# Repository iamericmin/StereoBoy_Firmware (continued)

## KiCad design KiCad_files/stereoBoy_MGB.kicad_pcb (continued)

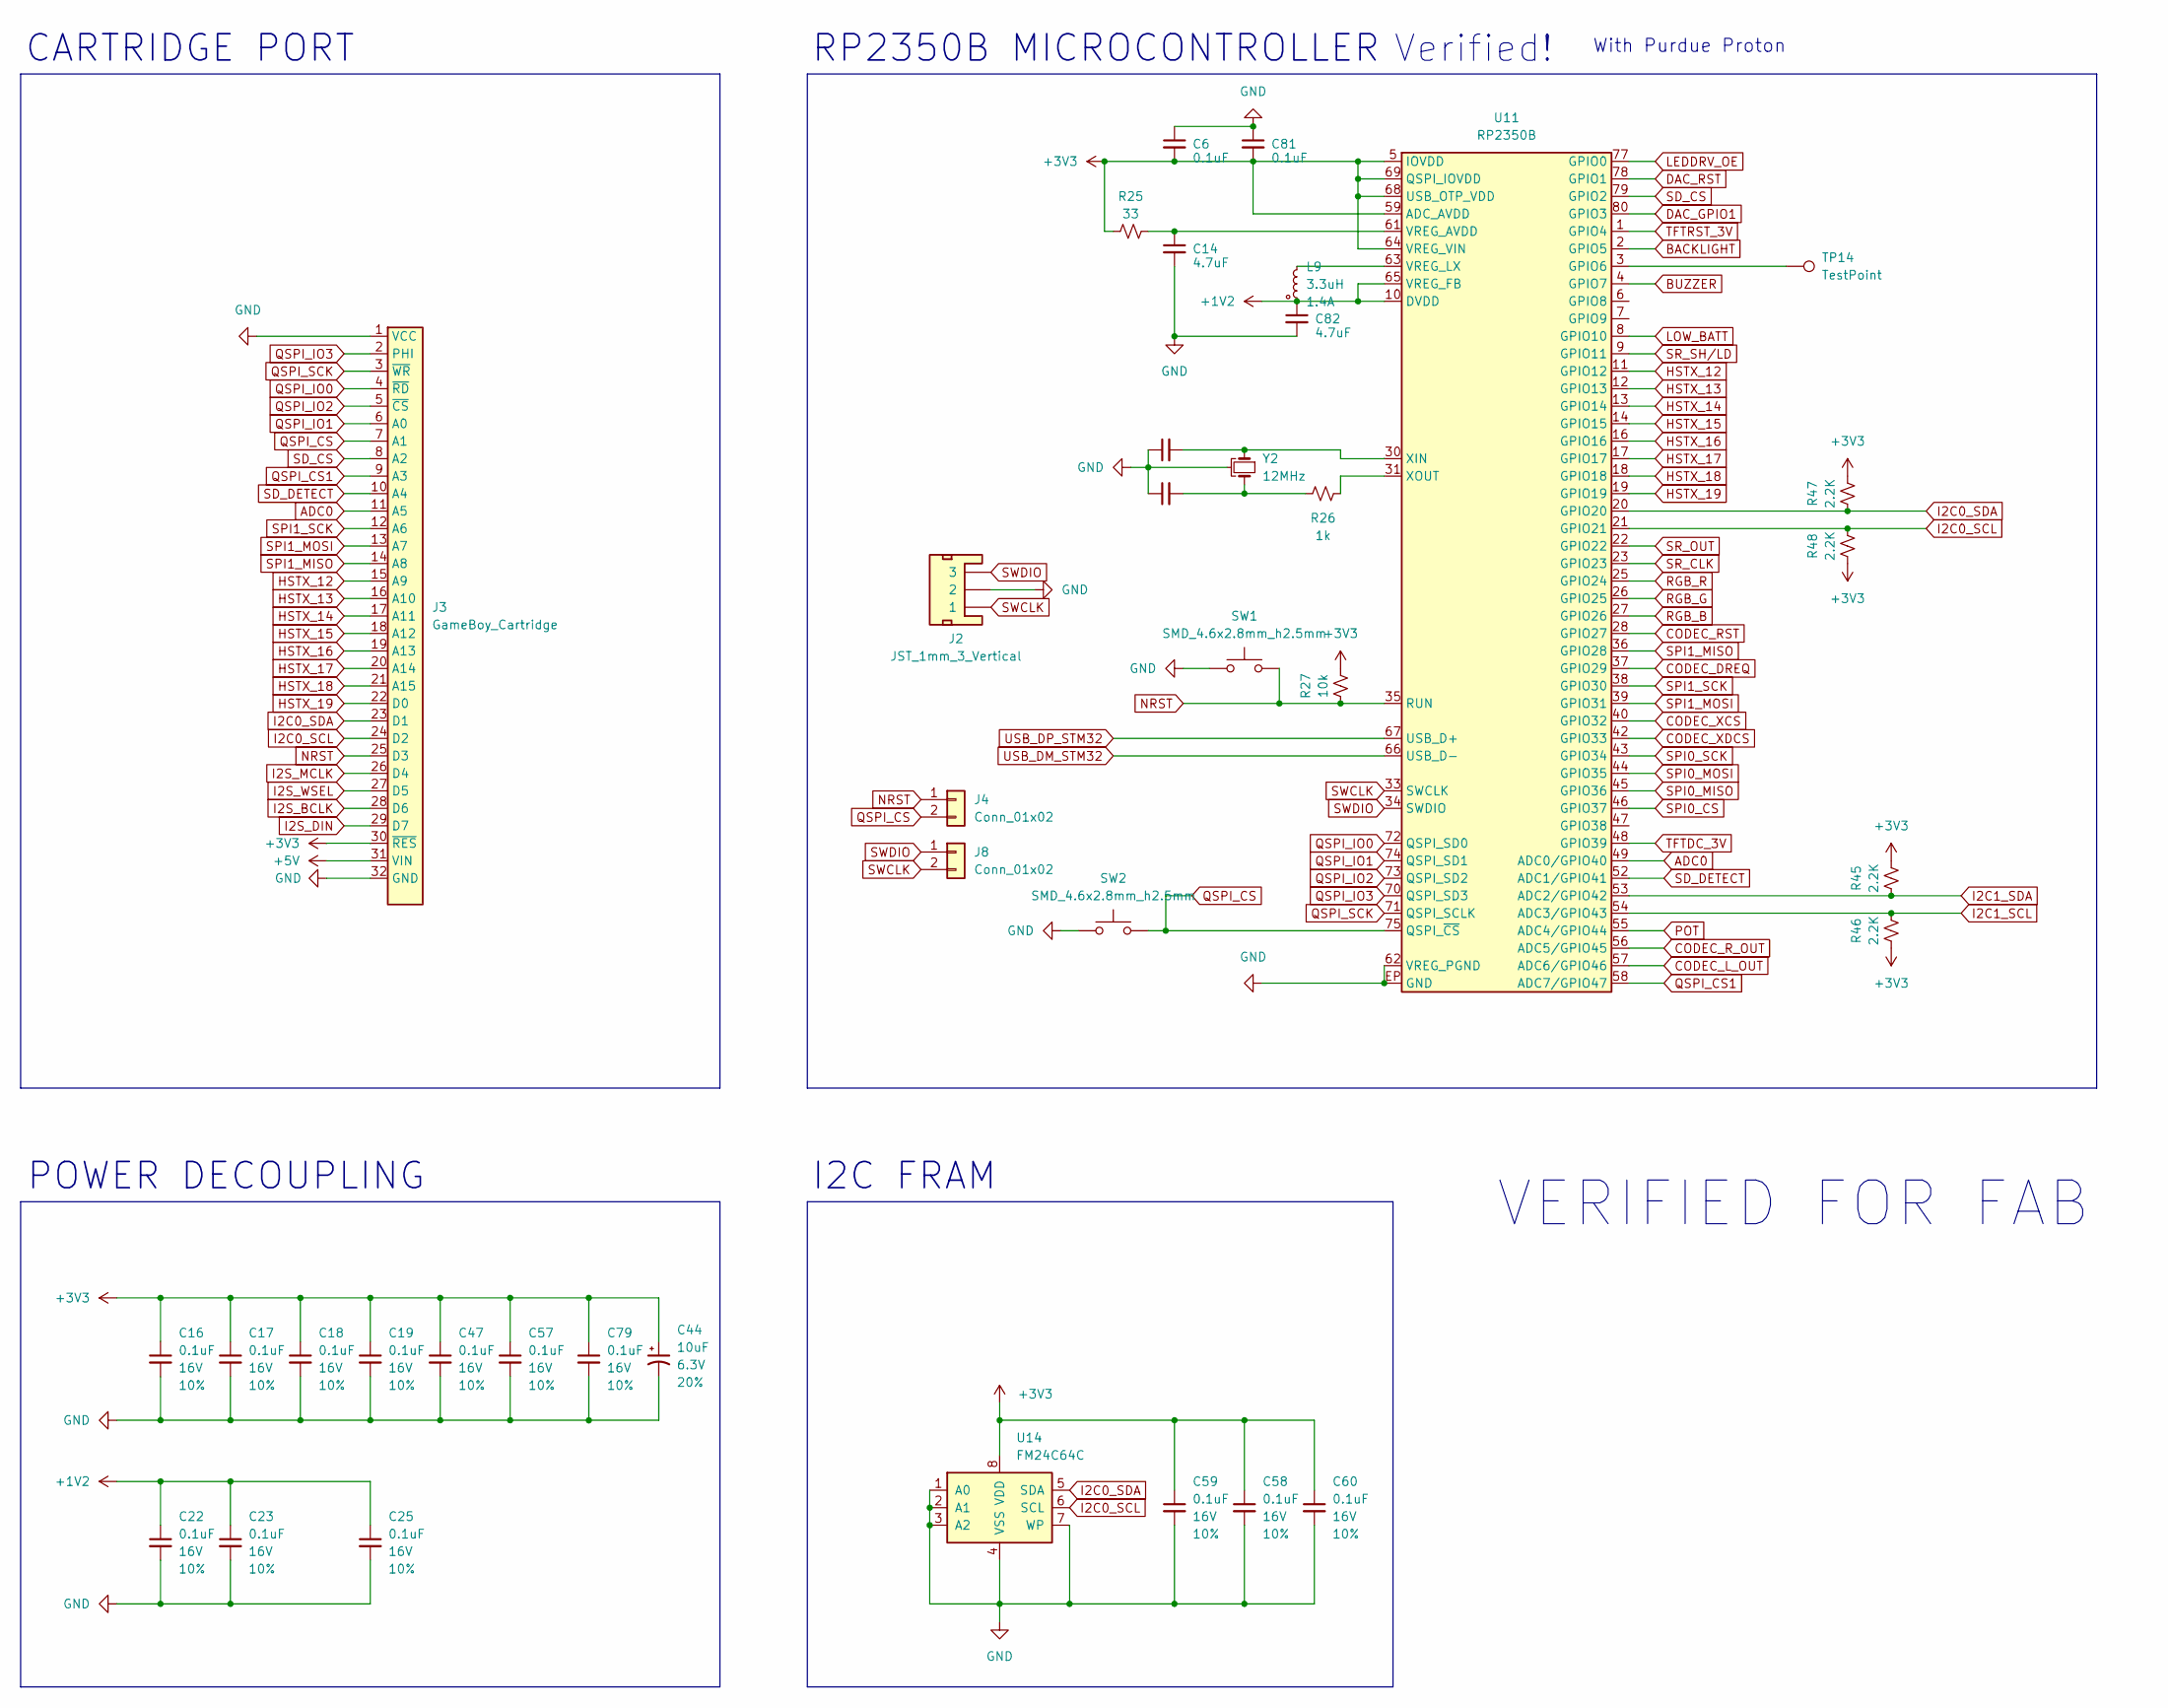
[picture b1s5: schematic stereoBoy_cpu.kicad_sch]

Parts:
C6: 0.1uF; C_0402_1005Metric
C14: 4.7uF; C_0402_1005Metric
C16, C17, C18, C19, C22, C23, C25, C47, C57, C58, C60, C79: 0.1uF; C_0402_1005Metric; Voltage 16V; Tolerance 10%
C20, C21: 15pF; C_0402_1005Metric; Voltage 50V; Tolerance 5%
C44: 10uF; CP_Elec_6.3x4.5; Voltage 6.3V; Tolerance 20%
C59: 0.1uF; C_0805_2012Metric; Voltage 16V; Tolerance 10%
C81: 0.1uF; WAi_0402_1005Metric
C82: 4.7uF; WAi_0402_1005Metric
J2: JST_1mm_3_Vertical; JST_1x03_P1.0mm_Horizontal_SMD
J3: GameBoy_Cartridge; MGB-CART-CONN
J4, J8: Conn_01x02; 1x02_P2.54mm
L9: 3.3uH; L_Cenker_CKCS201610
R25: 33; R_0402_1005Metric
R26: 1k; R_0402_1005Metric
R27: 10k; R_0603_1608Metric
R45, R46, R47, R48: 2.2K; R_0402_1005Metric
SW1, SW2: SMD_4.6x2.8mm_h2.5mm; Push_SMD_4.6x2.8mm_h2.5mm
TP14: TestPoint; TestPoint_Pad_D1.0mm
U11: RP2350B; QFN-80-1EP_10x10mm_P0.4mm_EP3.4x3.4mm
U14: FM24C64C; SOIC-8_3.9x4.9mm_P1.27mm
Y2: 12MHz; Crystal_SMD_3225-4Pin_3.2x2.5mm

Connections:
+1V2: C22.1, C23.1, C25.1, C82.1, L9.1, U11.10 (DVDD), U11.32 (DVDD), U11.51 (DVDD), U11.65 (VREG_FB)
+3V3: C6.2, C16.1, C17.1, C18.1, C19.1, C44.1, C47.1, C57.1, C58.1, C59.1, C60.1, C79.1, C81.2, J3.30 (~RES), R25.1, R27.2, R45.2, R46.1, R47.2, R48.1, U11.5 (IOVDD), U11.15 (IOVDD), U11.24 (IOVDD), U11.29 (IOVDD), U11.41 (IOVDD), U11.50 (IOVDD), U11.59 (ADC_AVDD), U11.60 (IOVDD), U11.64 (VREG_VIN), U11.68 (USB_OTP_VDD), U11.69 (QSPI_IOVDD), U11.76 (IOVDD), U14.8 (VDD); also elsewhere on the board
+5V: J3.31 (VIN); also elsewhere on the board
ADC0: J3.11 (A5), U11.49 (ADC0/GPIO40)
BACKLIGHT: U11.2 (GPIO5); also elsewhere on the board
BUZZER: U11.4 (GPIO7); also elsewhere on the board
CODEC_DREQ: U11.37 (GPIO29); also elsewhere on the board
CODEC_L_OUT: U11.57 (ADC6/GPIO46); also elsewhere on the board
CODEC_RST: U11.28 (GPIO27); also elsewhere on the board
CODEC_R_OUT: U11.56 (ADC5/GPIO45); also elsewhere on the board
CODEC_XCS: U11.40 (GPIO32); also elsewhere on the board
CODEC_XDCS: U11.42 (GPIO33); also elsewhere on the board
DAC_GPIO1: U11.80 (GPIO3); also elsewhere on the board
DAC_RST: U11.78 (GPIO1); also elsewhere on the board
GND: C6.1, C14.2, C16.2, C17.2, C18.2, C19.2, C20.1, C21.1, C22.2, C23.2, C25.2, C44.2, C47.2, C57.2, C58.2, C59.2, C60.2, C79.2, C81.1, C82.2, J2.2, J3.1 (VCC), J3.32 (GND), SW1.1, SW2.1, U11.62 (VREG_PGND), U11.EP (GND), U14.1 (A0), U14.2 (A1), U14.3 (A2), U14.4 (VSS), U14.7 (WP), Y2.2, Y2.4; also elsewhere on the board
HSTX_12: J3.15 (A9), U11.11 (GPIO12)
HSTX_13: J3.16 (A10), U11.12 (GPIO13)
HSTX_14: J3.17 (A11), U11.13 (GPIO14)
HSTX_15: J3.18 (A12), U11.14 (GPIO15)
HSTX_16: J3.19 (A13), U11.16 (GPIO16)
HSTX_17: J3.20 (A14), U11.17 (GPIO17)
HSTX_18: J3.21 (A15), U11.18 (GPIO18)
HSTX_19: J3.22 (D0), U11.19 (GPIO19)
I2C0_SCL: J3.24 (D2), R48.2, U11.21 (GPIO21), U14.6 (SCL); also elsewhere on the board
I2C0_SDA: J3.23 (D1), R47.1, U11.20 (GPIO20), U14.5 (SDA); also elsewhere on the board
I2C1_SCL: R46.2, U11.54 (ADC3/GPIO43); also elsewhere on the board
I2C1_SDA: R45.1, U11.53 (ADC2/GPIO42); also elsewhere on the board
I2S_BCLK: J3.28 (D6); also elsewhere on the board
I2S_DIN: J3.29 (D7); also elsewhere on the board
I2S_MCLK: J3.26 (D4); also elsewhere on the board
I2S_WSEL: J3.27 (D5); also elsewhere on the board
LEDDRV_OE: U11.77 (GPIO0); also elsewhere on the board
LOW_BATT: U11.8 (GPIO10); also elsewhere on the board
NRST: J3.25 (D3), J4.1, R27.1, SW1.2, U11.35 (RUN)
unnamed: C21.2, R26.1, Y2.3
unnamed: TP14.1, U11.3 (GPIO6)
unnamed: C14.1, R25.2, U11.61 (VREG_AVDD)
unnamed: L9.2, U11.63 (VREG_LX)
unnamed: C20.2, U11.30 (XIN), Y2.1
unnamed: R26.2, U11.31 (XOUT)
POT: U11.55 (ADC4/GPIO44); also elsewhere on the board
QSPI_CS: J3.7 (A1), J4.2, SW2.2, U11.75 (QSPI_~CS)
QSPI_CS1: J3.9 (A3), U11.58 (ADC7/GPIO47)
QSPI_IO0: J3.4 (~RD), U11.72 (QSPI_SD0)
QSPI_IO1: J3.6 (A0), U11.74 (QSPI_SD1)
QSPI_IO2: J3.5 (~CS), U11.73 (QSPI_SD2)
QSPI_IO3: J3.2 (PHI), U11.70 (QSPI_SD3)
QSPI_SCK: J3.3 (~WR), U11.71 (QSPI_SCLK)
RGB_B: U11.27 (GPIO26); also elsewhere on the board
RGB_G: U11.26 (GPIO25); also elsewhere on the board
RGB_R: U11.25 (GPIO24); also elsewhere on the board
SD_CS: J3.8 (A2), U11.79 (GPIO2)
SD_DETECT: J3.10 (A4), U11.52 (ADC1/GPIO41)
SPI0_CS: U11.46 (GPIO37); also elsewhere on the board
SPI0_MISO: U11.45 (GPIO36); also elsewhere on the board
SPI0_MOSI: U11.44 (GPIO35); also elsewhere on the board
SPI0_SCK: U11.43 (GPIO34); also elsewhere on the board
SPI1_MISO: J3.14 (A8), U11.36 (GPIO28); also elsewhere on the board
SPI1_MOSI: J3.13 (A7), U11.39 (GPIO31); also elsewhere on the board
SPI1_SCK: J3.12 (A6), U11.38 (GPIO30); also elsewhere on the board
SR_CLK: U11.23 (GPIO23); also elsewhere on the board
SR_OUT: U11.22 (GPIO22); also elsewhere on the board
SR_SH/LD: U11.9 (GPIO11); also elsewhere on the board
SWCLK: J2.1, J8.2, U11.33 (SWCLK)
SWDIO: J2.3, J8.1, U11.34 (SWDIO)
TFTDC_3V: U11.48 (GPIO39); also elsewhere on the board
TFTRST_3V: U11.1 (GPIO4); also elsewhere on the board
USB_DM_STM32: U11.66 (USB_D-); also elsewhere on the board
USB_DP_STM32: U11.67 (USB_D+); also elsewhere on the board

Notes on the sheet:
VERIFIED FOR FAB
With Purdue Proton
I2C FRAM
POWER DECOUPLING
Verified!
CARTRIDGE PORT
RP2350B MICROCONTROLLER

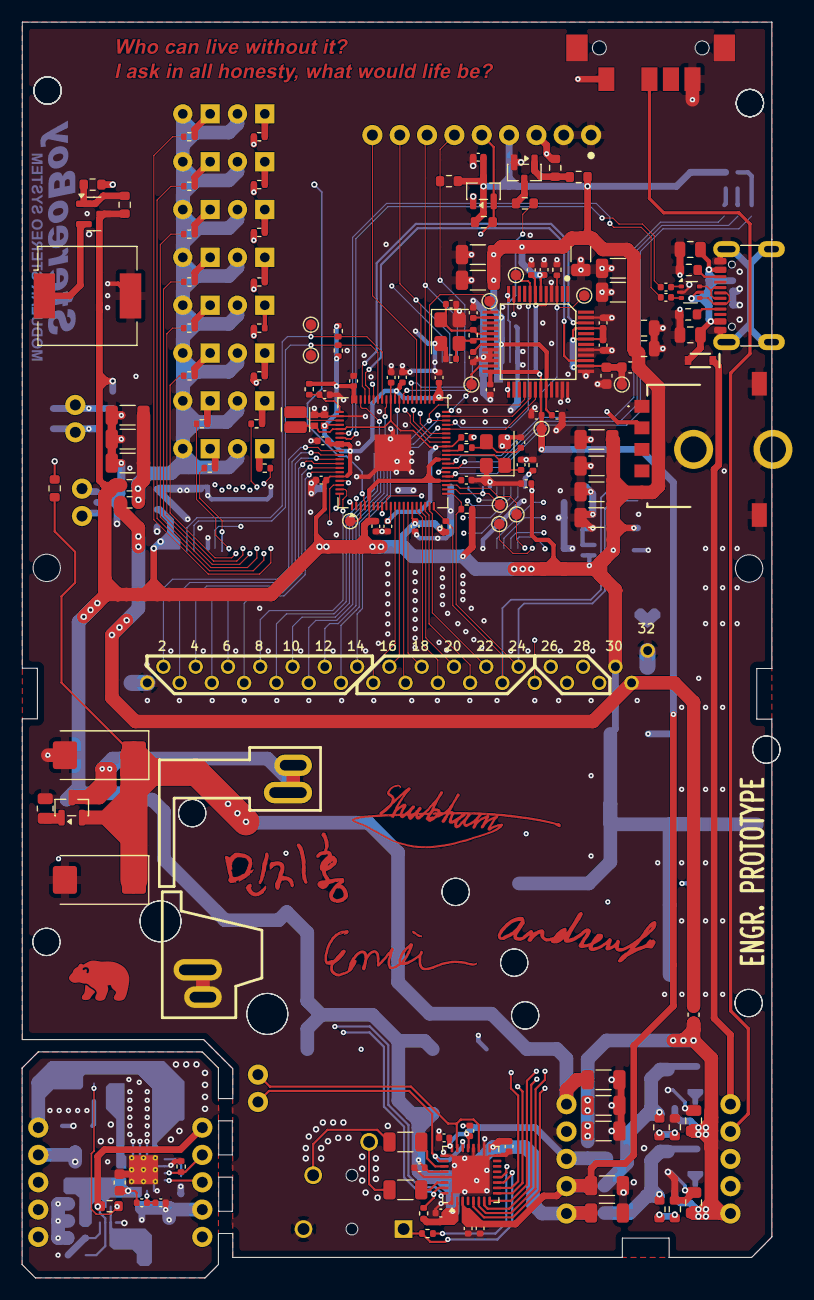
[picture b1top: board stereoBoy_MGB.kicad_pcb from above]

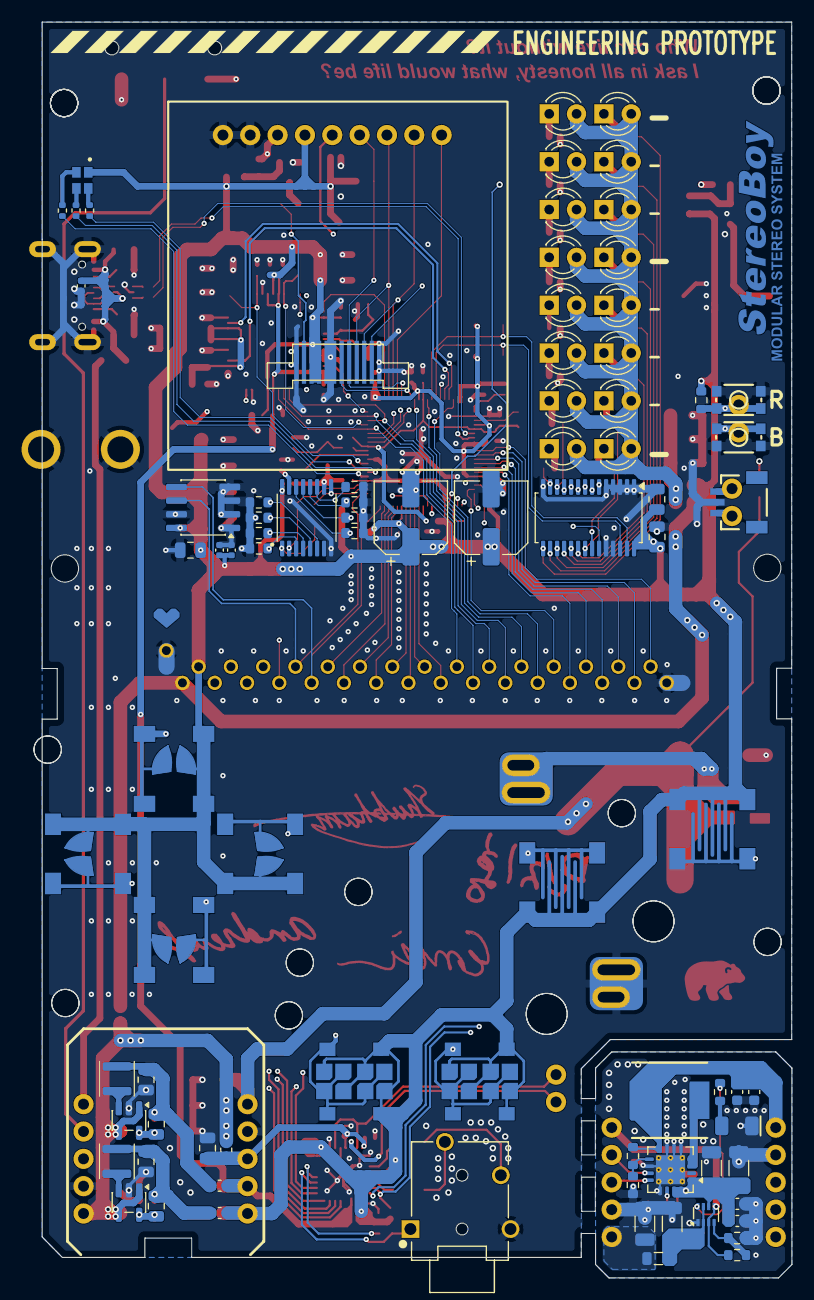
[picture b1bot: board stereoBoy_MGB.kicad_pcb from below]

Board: 4 copper layers, 69.7 x 116.7 mm, 249 parts (84 on the bottom side), 165 nets.

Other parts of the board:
UNK_HOLE_0: dummyfp0
UNK_HOLE_1: dummyfp1
UNK_HOLE_4: dummyfp4
UNK_HOLE_5: dummyfp5
UNK_HOLE_6: dummyfp6
UNK_HOLE_7: dummyfp7
UNK_HOLE_8: dummyfp8
UNK_HOLE_9: dummyfp9
UNK_HOLE_10: dummyfp10
UNK_HOLE_11: dummyfp11
UNK_HOLE_12: dummyfp12

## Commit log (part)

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2026-04-29 I have no idea what's in these changes
2026-05-07 asdf
2026-05-09 fixed annoying volume issue
2026-05-09 now skips to audio beginning when <prev> after 5s
2026-05-09 starting work on optimizing boot time. Got raw track scan working.
2026-05-09 much faster boot times but still too slow. implemented fast MD extraction as a band-aid
2026-05-09 idfk
2026-05-09 started working on folders
2026-05-10 added back VU meter turn off option
2026-05-11 what
2026-05-13 minor volume fix - moved potVal reading from addIcons to core1_entry
2026-05-28 started working on in-playback menu
2026-05-28 VU meter now active in playback menu and album art
2026-05-28 visualizer preservation working with in-playback menu
2026-06-21 working on cached artwork
2026-06-21 album cache workinggit add .!
2026-06-21 cached art working!
2026-06-21 culling dependencies for on-board image decoding
2026-06-27 minor sd card fixes
2026-06-28 fixed SD card mount but not sure
2026-06-28 started work on entirely cache-based UI
